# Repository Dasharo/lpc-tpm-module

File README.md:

# LPC TPM module

TPM module PCB project for platforms with 2x5 pin, 2.54mm pitch LPC header
and 2x10 pin, 2.54mm pitch LPC header compatible with PC Engines platforms.

## Description

Trusted Platform Module compatible with:

1. 2x5pin LPC header populated on:
  * PC Engines apu3 platforms (from apu3d revision and onwards)
  * PC Engines apu4 platforms (from apu4c revision and onwards)
  * PC Engines apu6 platforms (all revisions)
2. 2x10pin LPC header populated on:
  * PC Engines apu2 platforms (all revisions)
  * PC Engines apu1 platforms (all revisions).

Design based on original [PC Engines TPM1A](https://pcengines.ch/schema/tpm1a.pdf).

TPM module can be used for:

* disk encryption
* password protection
* platform integrity and other security issues

TPM module features:

* TPM Infineon SLB9665TT2.0
* Operating voltage 3-3.3V
* Meeting Intel TXT, Microsoft Windows and Google Chromebook certification
  criteria for successful platform qualification
* True Random Number Generator (TRNG)
* Full personalization with Endorsement Key (EK) and EK certificate
* Supports the LPC interface

## Pinout

The pin layout is compatible with PC Engines platforms:

1. 2x5pin LPC header:

2. 2x10pin LPC header:

## License

* Hardware is licensed under [CERN license](LICENSE.txt)
* Documentation is licensed under [CC BY-SA license](https://creativecommons.org/licenses/by-sa/2.0/)

## Where can I buy this product?

If you are not the enthusiast of DYI, then the plug and play product can be
bought in the [3mdeb shop](https://shop.3mdeb.com/product-category/modules/).

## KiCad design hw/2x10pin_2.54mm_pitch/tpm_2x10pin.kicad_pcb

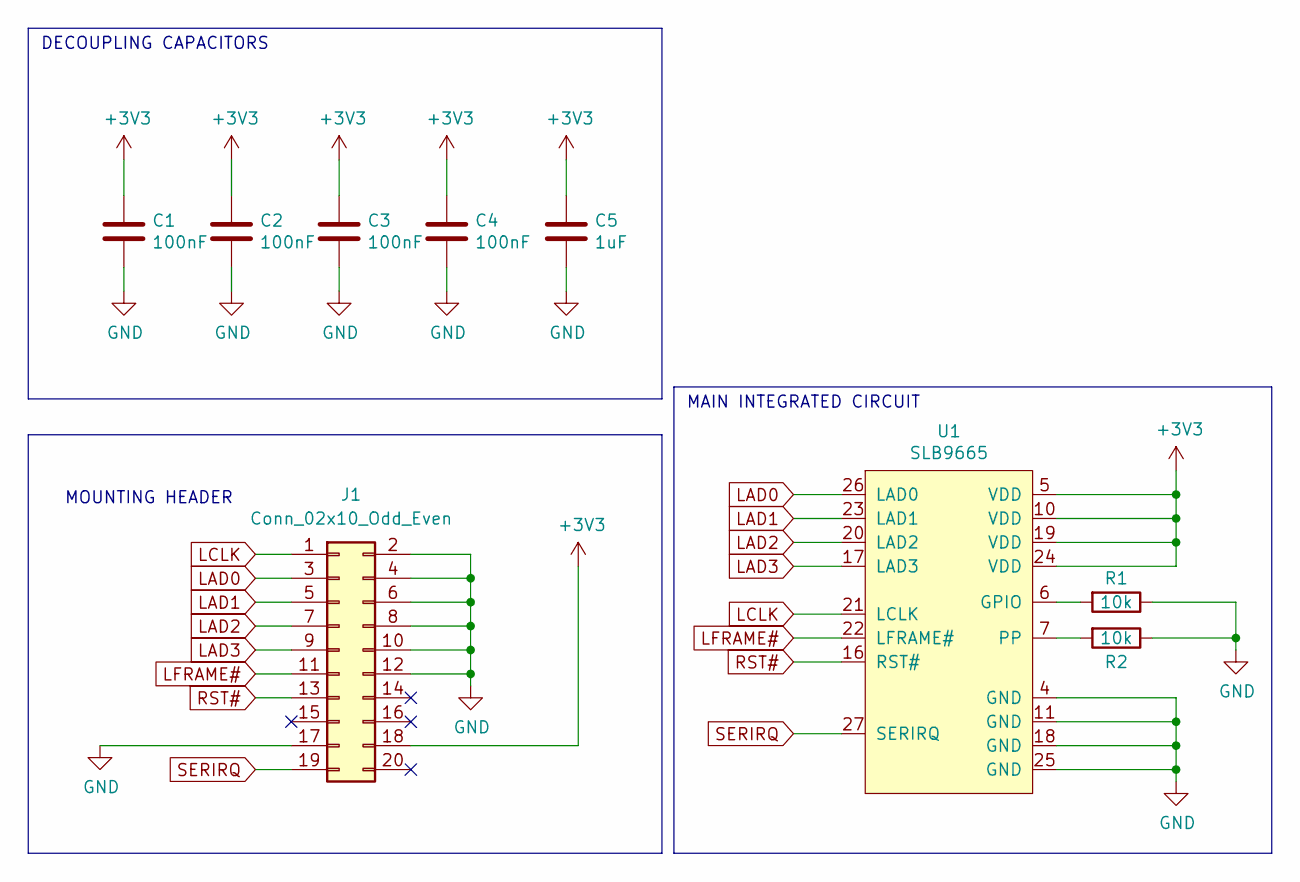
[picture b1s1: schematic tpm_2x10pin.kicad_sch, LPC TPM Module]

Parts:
C1, C2, C3, C4: 100nF; C_0603_1608Metric
C5: 1uF; C_0603_1608Metric
J1: Conn_02x10_Odd_Even; PinSocket_2x10_P2.54mm_Vertical
R1, R2: 10k; R_0603_1608Metric
U1: SLB9665; TSSOP-28_4.4x9.7mm_P0.65mm

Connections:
+3V3: C1.1, C2.1, C3.1, C4.1, C5.1, J1.18, U1.5 (VDD), U1.10 (VDD), U1.19 (VDD), U1.24 (VDD)
GND: C1.2, C2.2, C3.2, C4.2, C5.2, J1.2, J1.4, J1.6, J1.8, J1.10, J1.12, J1.17, R1.1, R2.1, U1.4 (GND), U1.11 (GND), U1.18 (GND), U1.25 (GND)
LAD0: J1.3, U1.26 (LAD0)
LAD1: J1.5, U1.23 (LAD1)
LAD2: J1.7, U1.20 (LAD2)
LAD3: J1.9, U1.17 (LAD3)
LCLK: J1.1, U1.21 (LCLK)
LFRAME#: J1.11, U1.22 (LFRAME#)
unnamed: R1.2, U1.6 (GPIO)
unnamed: R2.2, U1.7 (PP)
RST#: J1.13, U1.16 (RST#)
SERIRQ: J1.19, U1.27 (SERIRQ)

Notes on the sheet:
DECOUPLING CAPACITORS
MAIN INTEGRATED CIRCUIT
MOUNTING HEADER

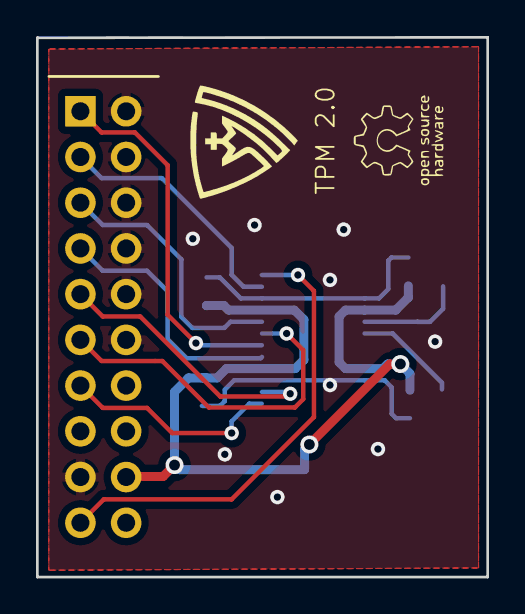
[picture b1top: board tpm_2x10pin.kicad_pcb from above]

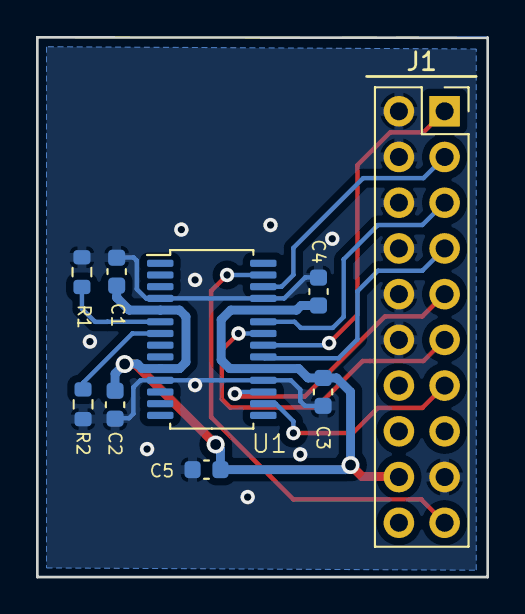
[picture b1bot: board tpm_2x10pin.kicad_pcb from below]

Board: 2 copper layers, 25.0 x 30.0 mm, 9 parts (9 on the bottom side), 12 nets.

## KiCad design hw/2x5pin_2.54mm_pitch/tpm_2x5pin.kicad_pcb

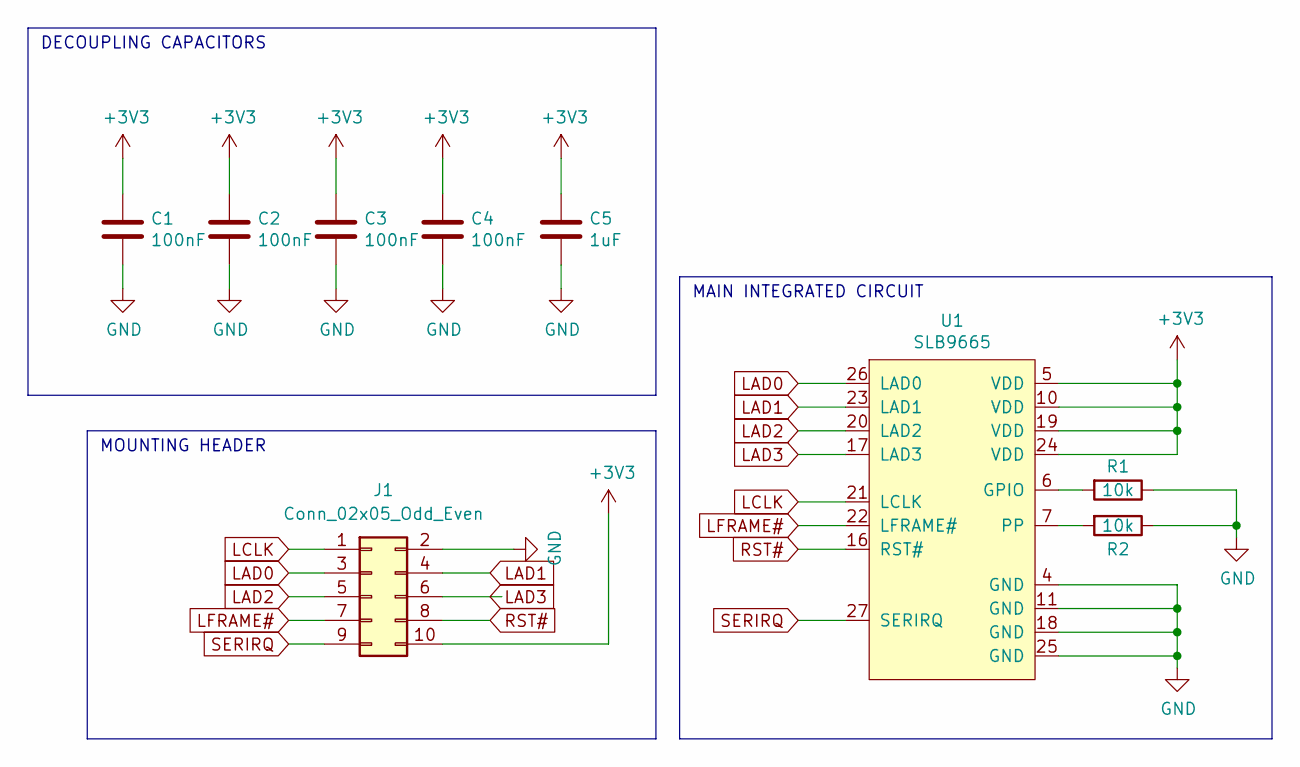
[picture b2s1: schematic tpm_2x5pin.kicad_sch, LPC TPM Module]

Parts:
C1, C2, C3, C4: 100nF; C_0603_1608Metric
C5: 1uF; C_0603_1608Metric
J1: Conn_02x05_Odd_Even; PinSocket_2x05_P2.54mm_Vertical
R1, R2: 10k; R_0603_1608Metric
U1: SLB9665; TSSOP-28_4.4x9.7mm_P0.65mm

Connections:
+3V3: C1.1, C2.1, C3.1, C4.1, C5.1, J1.10, U1.5 (VDD), U1.10 (VDD), U1.19 (VDD), U1.24 (VDD)
GND: C1.2, C2.2, C3.2, C4.2, C5.2, J1.2, R1.1, R2.1, U1.4 (GND), U1.11 (GND), U1.18 (GND), U1.25 (GND)
LAD0: J1.3, U1.26 (LAD0)
LAD1: J1.4, U1.23 (LAD1)
LAD2: J1.5, U1.20 (LAD2)
LAD3: J1.6, U1.17 (LAD3)
LCLK: J1.1, U1.21 (LCLK)
LFRAME#: J1.7, U1.22 (LFRAME#)
unnamed: R1.2, U1.6 (GPIO)
unnamed: R2.2, U1.7 (PP)
RST#: J1.8, U1.16 (RST#)
SERIRQ: J1.9, U1.27 (SERIRQ)

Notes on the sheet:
DECOUPLING CAPACITORS
MAIN INTEGRATED CIRCUIT
MOUNTING HEADER

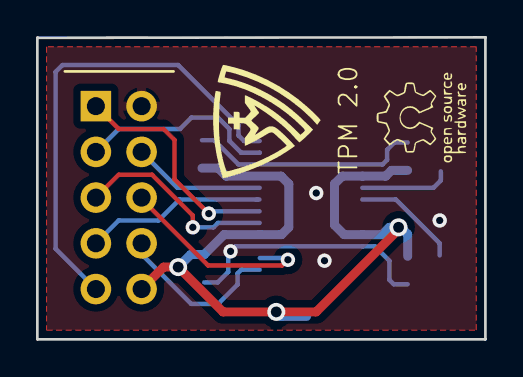
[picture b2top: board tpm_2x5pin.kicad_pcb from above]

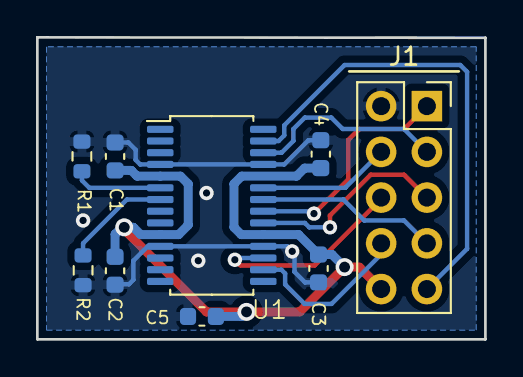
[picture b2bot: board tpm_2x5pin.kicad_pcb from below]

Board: 2 copper layers, 24.9 x 16.8 mm, 9 parts (9 on the bottom side), 12 nets.

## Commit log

2023-12-13 Add 2x5pin LPC header 2.54mm pitch TPM project
2023-12-13 Add 2x10pin LPC header 2.54mm pitch TPM project
2023-12-13 img: Add headers images
2023-12-13 README.md: udpate TPM module name
2023-12-13 hw/2x10pin_2.54mm_pitch: Update proejct files with proper BOM
2023-12-19 Add UserComments layer with board setup and characteristics
2024-03-20 README: link-to-shop-update
